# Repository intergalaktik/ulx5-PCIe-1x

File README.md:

# Work in progress!!! 

# ULX-PCIe
GateMate FPGA on PCIe card

## References

https://github.com/intergalaktik/ulx5m-gs

https://github.com/OLIMEX/GateMateA1-EVB

https://github.com/intergalaktik/Extension_Boards_for_Olimex_GateMate

https://github.com/YosysHQ/prjpeppercorn-test-cases

https://github.com/YosysHQ/prjpeppercorn
  
https://github.com/chili-chips-ba/openCologne

https://www.chili-chips.xyz/open-cologne

## Acknowledgements

This project was done in collaboration with Chili Chips*Ba team. 
They have put enormes effort in making all cores to work on GateMate even before we have our own board!
Thanks to them now we have big set of cores that can be used to check and improve opensource toolchain!
They are proven to be reliable partners that solves problem quickly and on side works on educating younger generations!
Also big thanks goes to YosysHQ as they are doing miracles with open source tooling, and we now finaly have one that works for GateMate!
From YosysHQ special thanks to Micko and Lofty that are helping in real time on Discord!
Special thanks to Patrick from Cologne, as without him and rest of Cologne team we would not be able to get this project done.

## Work on this board is financed by NLnet foundation

https://nlnet.nl/project/openCologne/

https://nlnet.nl/project/OpenCologne-PCIe/

https://github.com/chili-chips-ba/openCologne-PCIE

This project was funded through the NGI0 Commons Fund, a fund established by NLnet with financial support from the European Commission's Next Generation Internet programme, under the aegis of DG Communications Networks, Content and Technology under grant agreement No 101135429. Additional funding is made available by the Swiss State Secretariat for Education, Research and Innovation (SERI).

## Check up our blogposts
Comming soon!!!

## Contact us

Discord: https://discord.gg/qwMUk6W

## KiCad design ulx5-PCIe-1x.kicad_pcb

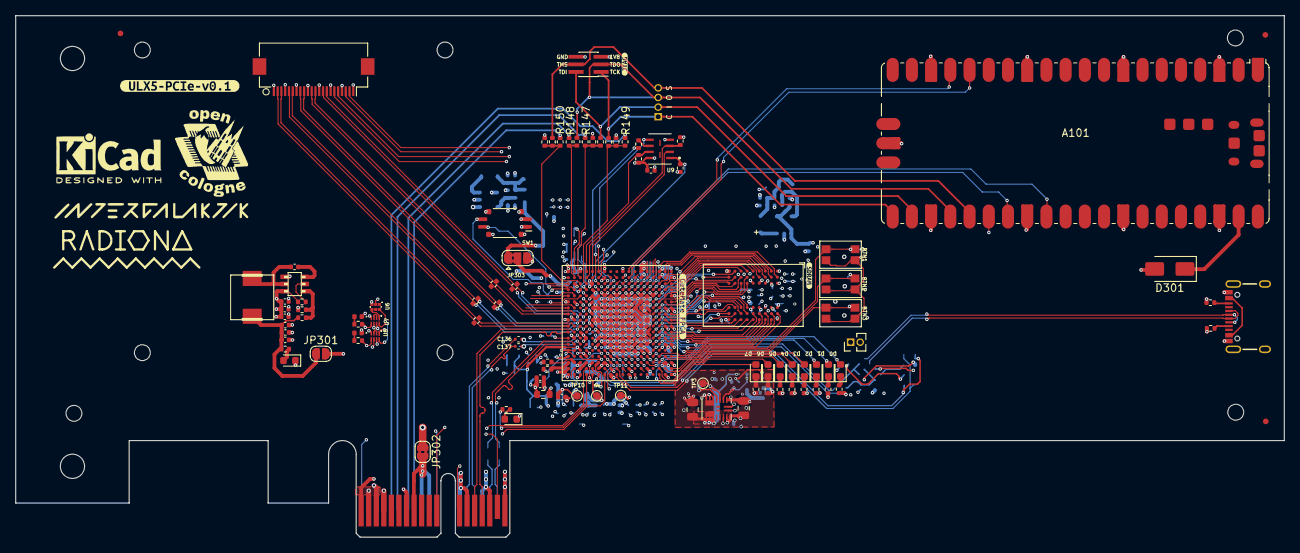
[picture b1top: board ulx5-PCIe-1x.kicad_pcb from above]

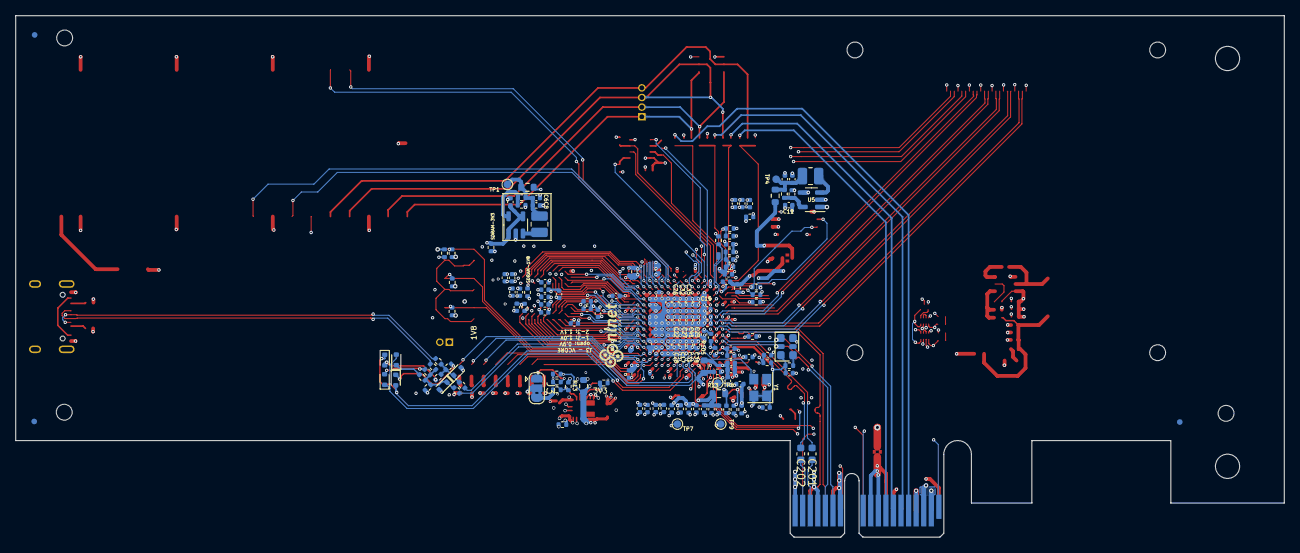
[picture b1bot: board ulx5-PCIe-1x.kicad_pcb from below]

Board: 6 copper layers, 167.7 x 68.9 mm, 261 parts (149 on the bottom side), 183 nets.

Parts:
A101: RaspberryPi_Pico; RaspberryPi_Pico_SMD
BTN1, BTN2, BTN3: SW_Push; Switch_EVPAA
C1, C10: 22u; C_0805_2012Metric
C2, C11: 4u7; C_0402_1005Metric
C4, C15, C18, C23, C28, C32, C35, C38, C41, C126: 10n; C_0402_1005Metric
C6, C24: 10u; C_0402_1005Metric
C8, C29: 1u; C_0402_1005Metric
C13, C16, C21, C26, C36, C44, C51, C54, C75, C78, C86, C90, C94, C100, C122, C123, C131: 2u2; C_0402_1005Metric
C14, C17, C22, C27, C31, C34, C37, C40, C42, C45, C47, C48, C49, C52, C55, C56, C57, C76, C79, C80, C88, C89, C92, C93, C96, C97, C102, C103, C127, C128, C132, C133, C138: 100n; C_0402_1005Metric
C33, C87, C91, C95, C120, C121: 220n; C_0402_1005Metric
C39, C43, C50, C53, C58, C77, C98, C124, C125: 22u; C_0402_1005Metric
C85: 2.2uF; C_0402_1005Metric
C99, C101, C140, C141: 22nF; C_0402_1005Metric
C136, C137: 100n; C_0402_SI_M
C201, C202: 100n; C_0603_1608Metric
C501, C507: 100nF/25V; C_0402_1005Metric
C503, C505, C509, C511, C513: 4u7/25V; C_0402_1005Metric
D1: green; D_0402_1005Metric
D2: red; D_0402_1005Metric
D3, D4: 3.6V; D_SOD-523
D5, D6, D7, D8: 1N914; D_SOD-523
D9, D10, D11, D12, D13, D14, D15, D16: LED; LED_0603_1608Metric
D301: D_Schottky; D_SMA
FID101, FID102, FID103, FID104, FID105, FID106: Fiducial; Fiducial_0.75mm_Mask1.5mm
H301, H302, H303, H304, H305, H306, H307: MountingHole_Pad; MountingHole_2.1mm
J1: PCIexpress_bracket; PCIexpress_bracket_low
J2: PCIexpress_x1
J3: Vcore_sel; SolderJumper-3_P1.3mm_Bridged2Bar12_RoundedPad1.0x1.5mm
J4: JTAG; PinHeader_2x03_P1.00mm_Vertical_SMD
J5: USB_C_Receptacle; USB-C_16
J101: JTAG_EXT; PinHeader_1x04_P1.27mm_Vertical
J102: 3V3_PSU; PinHeader_1x02_P1.27mm_Vertical
J303: Conn_01x22_Female; Hirose_FH12-22S-0.5SH_1x22-1MP_P0.50mm_Horizontal
JP301: Jumper_2_Open; SolderJumper-2_P1.3mm_Open_RoundedPad1.0x1.5mm
JP302: Jumper_2_Bridged; SolderJumper-2_P1.3mm_Bridged2Bar_RoundedPad1.0x1.5mm
JP303: LVDS-1V2-1V8; SolderJumper-3_P1.3mm_Bridged2Bar12_RoundedPad1.0x1.5mm
L1, L3: DFE322512F-2R2M=P2; L_1008_2520Metric
L501: 4.7uH_4A; YSPI0530
LED_P501, LED_P502: LowCur_green; LED_0603_1608Metric
LoGo_opencologne: MountingHole; open_cologne_small
R1, R2, R4, R143: 100k; R_0402_1005Metric
R3, R17, R18: 200k; R_0402_1005Metric
R7, R8, R116, R141, R142: 0R; R_0402_1005Metric
R9, R66, R115: dnp; R_0402_1005Metric
R10, R13, R21: 0R; R_0603_1608Metric
R12: 40k; R_0402_1005Metric
R14: 120k; R_0402_1005Metric
R15: 20k; R_0402_1005Metric
R16: 60k; R_0402_1005Metric
R23, R105, R106: 1R; R_0603_1608Metric
R24, R25, R27, R29, R30, R111: 10k; R_0402_1005Metric
R31, R32: 200R; R_0402_1005Metric
R33, R34, R35, R36, R38, R39: 4k7; R_0402_1005Metric
R37, R40, R41, R42, R43, R147, R148, R149, R150: 27R; R_0402_1005Metric
R44, R45: 27; R_0402_1005Metric
R46, R48, R58: 1k; R_0402_1005Metric
R47, R55: 12k1; R_0402_1005Metric
R59, R63, R64, R65, R86, R87, R88, R95, R118: R300; R_0402_1005Metric
R61, R62: 5k1; R_0402_1005Metric
R109: 200; R_0402_1005Metric
R121, R122, R123: 4R7; R_0402_1005Metric
R144, R145, R146: 1K; R_0402_1005Metric
R233, R234, R268, R271, R274: 150R; R_0402_1005Metric
R501: 100k 1%; R_0402_1005Metric
R503: 33k2 1%; R_0402_1005Metric
R504: 10k 1%; R_0402_1005Metric
R507, R508: 560R 1%; R_0402_1005Metric
REG501: TPS563201; SOT-23-THIN
SW1: 219-2MST; SW_DIP_SPSTx02_Slide_Copal_CVS-02xB_W5.9mm_P1mm
TP1: 1V8; TestPoint_Pad_D1.0mm
TP3: Vcore; TestPoint_Pad_D1.0mm
TP4: 1V2; TestPoint_Pad_D1.0mm
TP6: VDD_PLL; TestPoint_Pad_D1.0mm
TP7, TP9, TP11: GND; TestPoint_Pad_D1.0mm
TP8: VDD_SER_PLL; TestPoint_Pad_D1.0mm
TP10: VDD_SER; TestPoint_Pad_D1.0mm
TP12: SPI_FWD; TestPoint_Pad_1.0x1.0mm
U1, U5: TLV62569DBV; SOT-23-5
U3: MPM3833CGRH-Z
U4: GateMate-CCGM1A1; BGA-324_15.0x15.0mm_Layout18x18_P0.8mm_Ball0.45mm_Pad0.4mm_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
U6: 74LVC1G04GM,115; PESD3V3L5UF115
U7, U8: 74LVC2G00HK3-7; 74LVC2G00HK37
U9: AT25QL321-MBUE-T; SON80P400X300X60-10N
U10: IS42VM16320E; IS42S16320D-6BLI
X2: 511FCA100M000BAG; Oscillator_SMD_SiTime_PQFD-6L_3.2x2.5mm
Y1: ASE2-25.000MHZ-L-C-T; Crystal_SMD_TXC_7M-4Pin_3.2x2.5mm
kibuzzard-6ADB8C37: G***; kibuzzard-6ADB8C37
kibuzzard-686AA7AF: G***; kibuzzard-686AA7AF
kibuzzard-686AA726: G***; kibuzzard-686AA726
kibuzzard-686CE423: G***; kibuzzard-686CE423
radiona: radiona

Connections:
+1V2: JP303.1 (A), R21.2
+3V3: C1.1, C2.1, C11.1, C56.1, C57.1, C58.1, C75.1, C76.1, C94.1, C95.1, C96.1, C97.1, C98.1, C100.1, C102.1, C103.1, D301.2 (A), J102.1, J303.22, JP301.2 (B), JP302.1 (A), R1.1, R58.2, R115.2, R122.2, R144.1, R145.1, R146.1, U1.1 (EN), U1.4 (VIN), U3.13 (IN), U3.14 (IN), U4.A16 (VDD_EB), U4.B18 (VDD_EB), U4.E14 (VDD_EB), U4.E17 (VDD_EB), U4.F13 (VDD_EB), U4.G14 (VDD_EA), U4.H5 (VDD_WB), U4.H17 (VDD_EA), U4.J2 (VDD_WB), U4.J14 (VDD_EA), U4.K5 (VDD_WB), U4.L14 (VDD_EA), U4.L17 (VDD_EA), U4.M2 (VDD_WB), U4.M5 (VDD_WB), U5.1 (EN), U5.4 (VIN)
+3V3_PCIe: J2.A9 (+3.3V), J2.A10 (+3.3V), J2.B8 (+3.3V), JP302.2 (B)
/CLKREQ#: J2.B12 (RSVD), U4.M18 (IO_SB_B3)
/HighSpeed/CAM_GPIO0: J303.17, U4.N1 (IO_WB_A0)
/HighSpeed/CAM_GPIO1: J303.18, U4.N2 (IO_WB_B0)
/HighSpeed/LVDS0_C_N: J303.8, R268.2, U4.T9 (IO_SA_B6)
/HighSpeed/LVDS0_C_P: J303.9, R268.1, U4.R9 (IO_SA_A6)
/HighSpeed/LVDS0_D0_N: J303.2, R271.2, U4.V10 (IO_SA_B8)
/HighSpeed/LVDS0_D0_P: J303.3, R271.1, U4.U10 (IO_SA_A8)
/HighSpeed/LVDS0_D1_N: J303.5, R274.2, U4.T10 (IO_SA_B7)
/HighSpeed/LVDS0_D1_P: J303.6, R274.1, U4.R10 (IO_SA_A7)
/HighSpeed/LVDS0_D2_N: J303.11, R233.2, U4.V8 (IO_SA_B5)
/HighSpeed/LVDS0_D2_P: J303.12, R233.1, U4.U8 (IO_SA_A5)
/HighSpeed/LVDS0_D3_N: J303.14, R234.2, U4.T8 (IO_SA_B4)
/HighSpeed/LVDS0_D3_P: J303.15, R234.1, U4.R8 (IO_SA_A4)
/HighSpeed/SCL0: J303.20, U4.M3 (IO_WB_A1)
/HighSpeed/SDA0: J303.21, U4.M4 (IO_WB_B1)
/PCIexpress_connector/PCIe_CLK_N: C137.2, J2.A14 (REFCLK-)
/PCIexpress_connector/PCIe_CLK_P: C136.2, J2.A13 (REFCLK+)
/PCIexpress_connector/PCIe_RX_N: J2.B15 (PETn0), U4.V11 (SER_RX_N)
/PCIexpress_connector/PCIe_RX_P: J2.B14 (PETp0), U4.U11 (SER_RX_P)
/PCIexpress_connector/PCIe_TX_N: C202.2, U4.V13 (SER_TX_N)
/PCIexpress_connector/PCIe_TX_P: C201.1, U4.U13 (SER_TX_P)
/PCIexpress_connector/TCK: J2.A5 (TCK), R149.1
/PCIexpress_connector/TDI: J2.A6 (TDI), R147.1
/PCIexpress_connector/TDO: J2.A7 (TDO), R148.1
/PCIexpress_connector/TMS: J2.A8 (TMS), R150.1
/PCIexpress_connector/_PER0_N: C202.1, J2.A17 (PERn0)
/PCIexpress_connector/_PER0_P: C201.2, J2.A16 (PERp0)
/PCIexpress_connector/~PRSNT1: J2.A1 (~PRSNT1), J2.B17 (~PRSNT2)
/PERST#: J2.A11 (~PERST), U4.R17 (IO_SB_A1)
/PEWAKE#: J2.B11 (~WAKE), U4.M17 (IO_SB_A3)
/Raspberry_Pico/PI_TCK: A101.21 (GPIO16), J4.1, J101.1, R40.2
/Raspberry_Pico/PI_TDI: A101.22 (GPIO17), J4.2, J101.2, R41.2
/Raspberry_Pico/PI_TDO: A101.24 (GPIO18), J4.3, J101.3, R42.2
/Raspberry_Pico/PI_TMS: A101.25 (GPIO19), J4.4, J101.4, R43.2
/config/+1V8_FLASH: C43.1, C44.1, C45.1, R123.1, U4.N5 (VDD_WA), U4.P3 (VDD_WA), U4.P5 (VDD_WA), U4.T1 (VDD_WA), U4.U3 (VDD_WA)
/config/CFG_DONE: U4.V3 (IO_WA_B2/CFG_DONE), U6.2 (A)
/config/JTAG_CFG_MD0: R29.1, U4.R5 (CFG_MD0/IO_WA_A0)
/config/JTAG_CFG_MD1: R27.1, U4.T5 (CFG_MD1/IO_WA_B0)
/config/JTAG_CFG_MD2: R25.1, SW1.4, U4.U4 (CFG_MD2/IO_WA_A1)
/config/JTAG_CFG_MD3: R24.1, SW1.3, U4.V4 (CFG_MD3/IO_WA_B1)
/config/JTAG_POR: R30.1, R66.2, U4.U1 (POR_EN/IO_WA_A3)
/config/JTAG_TCK: R39.1, R40.1, R149.2, U4.R3 (JTAG_TCK/IO_WA_A5)
/config/JTAG_TDI: R36.2, R41.1, R147.2, U4.T2 (JTAG_TDI/IO_WA_A4)
/config/JTAG_TDO: R42.1, R148.2, U4.U2 (JTAG_TDO/IO_WA_B3)
/config/JTAG_TMS: R34.2, R43.1, R150.2, U4.T3 (JTAG_TMS/IO_WA_B4)
/config/SPI_CSN: R38.2, U4.N3 (IO_WA_A8/~SPI_CS), U9.1 (~CS)
/config/SPI_IO0: U4.P2 (IO_WA_B7/SPI_D0), U9.5 (SI/SIO0)
/config/SPI_IO1: U4.P1 (IO_WA_A7/SPI_D1), U9.2 (SO/SIO1)
/config/SPI_IO2: R35.2, U4.R2 (IO_WA_B6/SPI_D2), U9.3 (~WP/SIO2)
/config/SPI_IO3: R33.2, U4.R1 (IO_WA_A6/SPI_D3), U9.7 (~RESET/SIO3)
/config/SPI_SCK: R37.1, U4.N4 (IO_WA_B8/SPI_CLK)
/config/~CFG_FAIL: U4.V2 (IO_WA_A2/~CFG_FAILED), U8.1 (1A)
/ethernet/ALED0: D9.1 (K), R59.1
/ethernet/ALED1: D10.1 (K), R63.1
/ethernet/ALED2: D11.1 (K), R64.1
/ethernet/ALED3: D12.1 (K), R65.1
/ethernet/ALED4: D13.1 (K), R86.1
/ethernet/ALED5: D14.1 (K), R87.1
/ethernet/ALED6: D15.1 (K), R88.1
/ethernet/ALED7: D16.1 (K), R95.1
/ethernet/BTN1: BTN1.2, R144.2, U4.C15 (IO_EB_B7)
/ethernet/BTN2: BTN2.2, R145.2, U4.A15 (IO_EB_B8)
/ethernet/BTN3: BTN3.2, R146.2, U4.B15 (IO_EB_A8)
/ethernet/FPD1+: J5.A6 (D+), J5.B6 (D+), R45.2
/ethernet/FPD1-: J5.A7 (D-), J5.B7 (D-), R44.2
/ethernet/LED0: D9.2 (A), U4.D15 (IO_EB_A7)
/ethernet/LED1: D10.2 (A), U4.C16 (IO_EB_B6)
/ethernet/LED2: D11.2 (A), U4.D16 (IO_EB_A6)
/ethernet/LED3: D12.2 (A), U4.A17 (IO_EB_B5)
/ethernet/LED4: D13.2 (A), U4.B17 (IO_EB_A5)
/ethernet/LED5: D14.2 (A), U4.C17 (IO_EB_B4)
/ethernet/LED6: D15.2 (A), U4.C18 (IO_EB_A4)
/ethernet/LED7: D16.2 (A), U4.E15 (IO_EB_B3)
/ethernet/USB25_N: R141.1, U4.L15 (IO_EA_B1), U4.M14 (IO_EA_B0)
/ethernet/USB25_P: R142.1, U4.L16 (IO_EA_A1), U4.M15 (IO_EA_A0)
/ethernet/USB_CC1: J5.A5 (CC1), R61.2
/ethernet/USB_CC2: J5.B5 (CC2), R62.2
/ethernet/USB_N: D4.1 (K), R44.1, R48.1, R55.2, R141.2
/ethernet/USB_P: D3.1 (K), R45.1, R46.2, R47.2, R58.1, R142.2
/ethernet/USB_PULL_N: D7.2 (A), D8.1 (K), U4.K17 (IO_EA_B2)
/ethernet/USB_PULL_P: D5.2 (A), D6.1 (K), U4.K18 (IO_EA_A2)
/lvds/+1V2_SA: C50.1, C51.1, C52.1, R121.2, U4.P6 (VDD_SA), U4.P8 (VDD_SA), U4.P10 (VDD_SA), U4.U6 (VDD_SA), U4.U9 (VDD_SA)
/lvds/+3V3_SB: C53.1, C54.1, C55.1, R122.1, U4.N11 (VDD_SB), U4.N13 (VDD_SB), U4.N18 (VDD_SB), U4.R15 (VDD_SB), U4.T18 (VDD_SB)
/lvds/CLK_25MHz: U4.N14 (CLK0/IO_SB_A8), Y1.3
/lvds/LED1#: R508.2, U4.R18 (IO_SB_B1)
/serdes/SER_CK_N: C137.1, U4.T13 (SER_CLK_N), X2.5 (OUT-)
/serdes/SER_CK_P: C136.1, U4.T12 (SER_CLK), X2.4 (OUT+)
/serdes/SER_PORT_ADJ: C133.1, U4.V15 (POR_ADJ)
EN_3V3: R501.2, REG501.5 (EN)
FPGA_GPIO1: A101.29 (GPIO22), U4.H3 (IO_WB_A8)
FPGA_GPIO2: A101.27 (GPIO21), U4.H4 (IO_WB_B8)
FPGA_UART_RX: A101.16 (GPIO12), U4.H2 (IO_WB_B7)
FPGA_UART_TX: A101.17 (GPIO13), U4.H1 (IO_WB_A7)
GND: A101.3 (GND), A101.8 (GND), A101.13 (GND), A101.18 (GND), A101.23 (GND), A101.28 (GND), A101.33 (AGND), A101.38 (GND), A101.D2 (GND), C1.2, C2.2, C4.1, C6.2, C8.2, C10.2, C11.2, C13.2, C14.2, C15.2, C16.2, C17.2, C18.2, C21.2, C22.2, C23.2, C24.2, C26.2, C27.2, C28.2, C29.2, C31.2, C32.2, C33.2, C34.2, C35.2, C36.2, C37.2, C38.2, C39.2, C40.2, C41.2, C42.2, C43.2, C44.2, C45.2, C47.2, C48.2, C49.2, C50.2, C51.2, C52.2, C53.2, C54.2, C55.2, C56.2, C57.2, C58.2, C75.2, C76.2, C77.2, C78.2, C79.2, C80.2, C85.2, C86.2, C87.2, C88.2, C89.2, C90.2, C91.2, C92.2, C93.2, C94.2, C95.2, C96.2, C97.2, C98.2, C99.2, C100.2, C101.2, C102.2, C103.2, C120.2, C121.2, C122.2, C123.2, C124.2, C125.2, C126.2, C127.2, C128.2, C131.2, C132.2, C133.2, C138.2, C140.2, C141.2, C501.2, C503.2, C505.2, C509.2, C511.2, C513.2, D1.1 (K), D2.1 (K), D3.2 (A), D4.2 (A), J2.A4 (GND), J2.A12 (GND), J2.A15 (GND), J2.A18 (GND), J2.B4 (GND), J2.B7 (GND), J2.B13 (GND), J2.B16 (GND), J2.B18 (GND), J3.2, J4.6, J5.GND, J5.S (SHIELD), J102.2, J303.1, J303.4, J303.7, J303.10, J303.13, J303.16, J303.19, LED_P501.1, LED_P502.1, R2.2, R4.2, R7.2, R8.2, R12.1, R18.2, R24.2, R25.2, R27.2, R29.2, R30.2, R39.2, R59.2, R61.1, R62.1, R63.2, R64.2, R65.2, R86.2, R87.2, R88.2, R95.2, R109.1, R118.2, R504.1, REG501.1 (GND), SW1.5, TP7.1 (1_1), TP9.1 (1_1), TP11.1 (1_1), U1.2 (GND), U3.1 (AGND), U3.16 (PGND), U4.A1 (GND), U4.A7 (GND), U4.A10 (GND), U4.A13 (GND), U4.A18 (GND), U4.B16 (GND), U4.C1 (GND), U4.E5 (GND), U4.E7 (GND), U4.E9 (GND), U4.E11 (GND), U4.E13 (GND), U4.E18 (GND), U4.F1 (GND), U4.F6 (GND), U4.F8 (GND), U4.F10 (GND), U4.F12 (GND), U4.F14 (GND), U4.G5 (GND), U4.G7 (GND), U4.G9 (GND), U4.G11 (GND), U4.G13 (GND), U4.H6 (GND), U4.H8 (GND), U4.H10 (GND), U4.H12 (GND), U4.H14 (GND), U4.H18 (GND), U4.J1 (GND), U4.J5 (GND), U4.J7 (GND), U4.J9 (GND), U4.J11 (GND), U4.J13 (GND), U4.K6 (GND), U4.K8 (GND), U4.K10 (GND), U4.K12 (GND), U4.K14 (GND), U4.L5 (GND), U4.L7 (GND), U4.L9 (GND), U4.L11 (GND), U4.L13 (GND), U4.L18 (GND), U4.M1 (GND), U4.M6 (GND), U4.M8 (GND), U4.M10 (GND), U4.M12 (GND), U4.M16 (GND), U4.N7 (GND), U4.N9 (GND), U4.N12 (GND), U4.N17 (GND), U4.P4 (GND), U4.P7 (GND), U4.P9 (GND), U4.R12 (GND), U4.R16 (GND), U4.T4 (GND), U4.T11 (GND), U4.T17 (GND), U4.U14 (GND), U4.U15 (GND), U4.V1 (GND), U4.V6 (GND), U4.V9 (GND), U4.V14 (GND), U4.V18 (GND), U5.2 (GND), U6.3 (GND), U7.4 (GND), U8.4 (GND), U9.4 (GND), U10.A1 (VSS), U10.A3 (VSSQ), U10.B7 (VSSQ), U10.C3 (VSSQ), U10.D7 (VSSQ), U10.E3 (VSS), U10.J1 (VSS), X2.3 (GND), Y1.2
unnamed: A101.39 (VSYS), D301.1 (K)
unnamed: BTN1.1, BTN2.1, BTN3.1, R118.1
unnamed: C6.1, C8.1, L1.2, R3.1, R10.1, TP1.1 (1_1)
unnamed: C24.1, C29.1, L3.2, R17.1, R21.1, TP4.1 (1_1)
unnamed: D1.2 (A), R31.2
unnamed: D2.2 (A), R32.2
unnamed: D5.1 (K), R46.1
unnamed: D6.2 (A), R47.1
unnamed: D7.1 (K), R48.2
unnamed: D8.2 (A), R55.1
unnamed: J3.1, R14.1
unnamed: J3.3, R16.1
unnamed: C49.1, JP303.2 (C), R121.1
unnamed: LED_P501.2, R507.1
unnamed: LED_P502.2, R508.1
unnamed: R7.1, U4.U16 (GND)
unnamed: R8.1, U4.V16 (GND)
unnamed: C507.1, L501.1, REG501.2 (SW)
unnamed: R503.1, R504.2, REG501.4 (VFB)
unnamed: C507.2, REG501.6 (VFST)
unnamed: R3.2, R4.1, U1.5 (FB)
unnamed: L1.1, U1.3 (SW)
unnamed: R1.2, R2.1, U3.4 (EN)
unnamed: R12.2, R14.2, R15.2, R16.2, U3.2 (FB)
unnamed: C10.1, R13.1, R15.1, TP3.1 (1_1), U3.3 (OUT_S), U3.8 (OUT), U3.9 (OUT), U3.10 (OUT)
unnamed: U3.5 (SW), U3.6 (SW), U3.7 (SW), U3.15 (SW)
unnamed: R109.2, U4.V12 (SER_RTERM)
unnamed: TP12.1 (1_1), U4.R4 (IO_WA_B5/SPI_FWD)
unnamed: R9.1, U4.N16 (NC)
unnamed: R17.2, R18.1, U5.5 (FB)
unnamed: L3.1, U5.3 (SW)
unnamed: U6.4 (Y), U7.1 (1A)
unnamed: U7.2 (1B), U7.3 (2Y)
unnamed: R31.1, U7.5 (2A), U7.7 (1Y)
unnamed: U8.2 (1B), U8.3 (2Y)
unnamed: R32.1, U8.5 (2A), U8.7 (1Y)
unnamed: R37.2, U9.6 (SCLK)
unnamed: R143.2, X2.1 (OE)
RST_N: A101.26 (GPIO20), C138.1, R111.2, U4.N15 (IO_SB_B8), U4.T15 (RST_N), U7.6 (2B), U8.6 (2B)
SDRAM_A0: U4.D10 (IO_NB_A1), U10.H7 (A0)
SDRAM_A1: U4.D11 (IO_NB_A3), U10.H8 (A1)
SDRAM_A2: U4.C10 (IO_NB_B1), U10.J8 (A2)
SDRAM_A3: U4.A9 (IO_NB_B0), U10.J7 (A3)
SDRAM_A4: U4.C6 (IO_NA_A3), U10.J3 (A4)
SDRAM_A5: U4.D6 (IO_NA_B3), U10.J2 (A5)
SDRAM_A6: U4.A6 (IO_NA_A4), U10.H3 (A6)
SDRAM_A7: U4.D7 (IO_NA_B5), U10.H2 (A7)
SDRAM_A8: U4.C5 (IO_NA_B2), U10.H1 (A8)
SDRAM_A9: U4.C7 (IO_NA_A5), U10.G3 (A9)
SDRAM_A10: U4.B9 (IO_NB_A0), U10.H9 (A10)
SDRAM_A11: U4.B6 (IO_NA_B4), U10.G2 (A11)
SDRAM_A12: U4.B5 (IO_NA_A2), U10.G1 (A12)
SDRAM_BA0: U4.B8 (IO_NA_B7), U10.G7 (BA0)
SDRAM_BA1: U4.C9 (IO_NA_A8), U10.G8 (BA1)
SDRAM_CKE: U4.C8 (IO_NA_A6), U10.F3 (CKE)
SDRAM_CLK: U4.D8 (IO_NA_B6), U10.F2 (CLK)
SDRAM_D0: U4.C14 (IO_NB_B8), U10.A8 (DQ0)
SDRAM_D1: U4.C13 (IO_NB_B6), U10.B9 (DQ1)
SDRAM_D2: U4.D14 (IO_NB_A8), U10.B8 (DQ2)
SDRAM_D3: U4.B12 (IO_NB_A4), U10.C9 (DQ3)
SDRAM_D4: U4.D13 (IO_NB_A6), U10.C8 (DQ4)
SDRAM_D5: U4.B11 (IO_NB_A2), U10.D9 (DQ5)
SDRAM_D6: U4.A12 (IO_NB_B4), U10.D8 (DQ6)
SDRAM_D7: U4.C12 (IO_NB_B5), U10.E9 (DQ7)
SDRAM_D8: U4.B4 (IO_NA_B1), U10.E1 (DQ8)
SDRAM_D9: U4.A3 (IO_NA_A0), U10.D2 (DQ9)
SDRAM_D10: U4.B3 (IO_NA_B0), U10.D1 (DQ10)
SDRAM_D11: U4.C3 (IO_WC_A7), U10.C2 (DQ11)
SDRAM_D12: U4.C4 (IO_WC_B7), U10.C1 (DQ12)
SDRAM_D13: U4.B2 (IO_WC_B8), U10.B2 (DQ13)
SDRAM_D14: U4.B1 (IO_WC_A8), U10.B1 (DQ14)
SDRAM_D15: U4.D4 (IO_WC_B6), U10.A2 (DQ15)
SDRAM_DQM0: U4.A11 (IO_NB_B2), U10.E8 (DQML)
SDRAM_DQM1: U4.A4 (IO_NA_A1), U10.F1 (DQMH)
SDRAM_VCC: C77.1, C78.1, C79.1, C80.1, C85.1, C86.1, C87.1, C88.1, C89.1, C90.1, C91.1, C92.1, C93.1, C99.1, C101.1, C140.1, C141.1, R115.1, R116.1, U4.A2 (VDD_WC), U4.A5 (VDD_NA), U4.B7 (VDD_NA), U4.B10 (VDD_NB), U4.B13 (VDD_NB), U4.C2 (VDD_WC), U4.D5 (VDD_WC), U4.E6 (VDD_NA), U4.E8 (VDD_NA), U4.E10 (VDD_NB), U4.E12 (VDD_NB), U4.F2 (VDD_WC), U4.F5 (VDD_WC), U4.F7 (VDD_NA), U4.F11 (VDD_NB), U10.A7 (VDDQ), U10.A9 (VDD), U10.B3 (VDDQ), U10.C7 (VDDQ), U10.D3 (VDDQ), U10.E7 (VDD), U10.J9 (VDD)
SDRAM_nCAS: U4.D9 (IO_NA_B8), U10.F7 (~CAS)
SDRAM_nCS: U4.C11 (IO_NB_B3), U10.G9 (~CS)
SDRAM_nRAS: U4.A8 (IO_NA_A7), U10.F8 (~RAS)
SDRAM_nWE: U4.D12 (IO_NB_A5), U10.F9 (~WE)
VCC_3V3: C509.1, C511.1, C513.1, JP301.1 (A), L501.2, R503.2, R507.2
VDD_CLK: C4.2, C47.1, C48.1, C126.1, C131.1, C132.1, J4.5, JP303.3 (B), R10.2, R33.1, R34.1, R35.1, R36.1, R38.1, R66.1, R111.1, R116.2, R123.2, R143.1, SW1.1, SW1.2, U4.T14 (VDD_CLK), U6.6 (VCC), U7.8 (VCC), U8.8 (VCC), U9.8 (VCC), X2.6 (VDD), Y1.1, Y1.4
VDD_CORE: C13.1, C14.1, C15.1, C16.1, C17.1, C18.1, C21.1, C22.1, C23.1, C26.1, C27.1, C28.1, C31.1, C32.1, C34.1, C35.1, C37.1, C38.1, C40.1, C41.1, C42.1, C127.1, C128.1, R13.2, R23.1, R105.1, R106.1, U4.F9 (VDD), U4.G6 (VDD), U4.G8 (VDD), U4.G10 (VDD), U4.G12 (VDD), U4.H7 (VDD), U4.H9 (VDD), U4.H11 (VDD), U4.H13 (VDD), U4.J6 (VDD), U4.J8 (VDD), U4.J10 (VDD), U4.J12 (VDD), U4.K7 (VDD), U4.K9 (VDD), U4.K11 (VDD), U4.K13 (VDD), U4.L6 (VDD), U4.L8 (VDD), U4.L10 (VDD), U4.L12 (VDD), U4.M7 (VDD), U4.M9 (VDD), U4.M11 (VDD), U4.M13 (VDD), U4.N6 (VDD), U4.N8 (VDD), U4.N10 (VDD)
VDD_PLL: C33.1, C36.1, C39.1, R23.2, TP6.1 (1_1), U4.P16 (VDD_PLL)
VDD_SER: C121.1, C123.1, C125.1, R9.2, R106.2, TP10.1 (1_1), U4.U12 (VDD_SER), U4.V17 (VDD_SER)
VDD_SER_PLL: C120.1, C122.1, C124.1, R105.2, TP8.1 (1_1), U4.T16 (VDD_SER_PLL)
V_IN_INT: C501.1, C503.1, C505.1, J2.A2 (+12V), J2.A3 (+12V), J2.B1 (+12V), J2.B2 (+12V), J2.B3 (+12V), R501.1, REG501.3 (IN)

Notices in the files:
parts and their libraries:
project_license: CERN-OHL-S v2
